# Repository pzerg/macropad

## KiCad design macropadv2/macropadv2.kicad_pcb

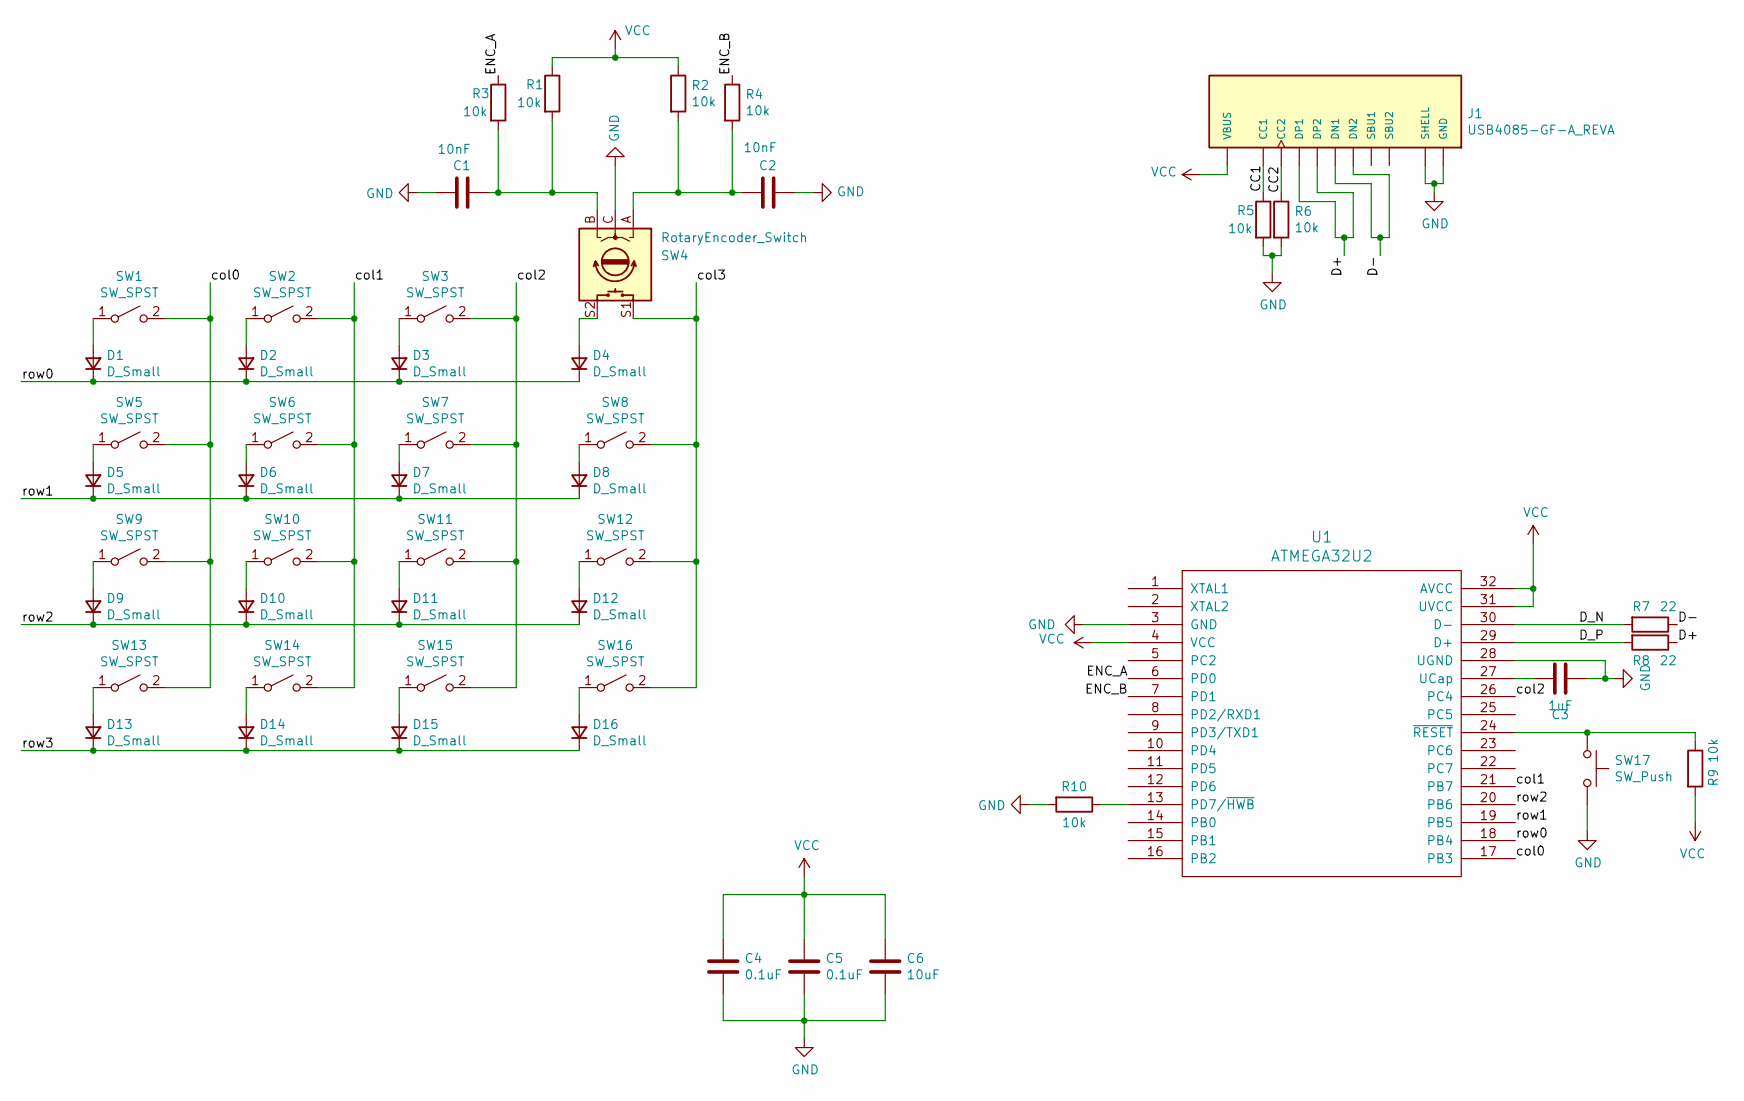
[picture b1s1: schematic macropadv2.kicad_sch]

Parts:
C1, C2: 10nF; C_0603_1608Metric
C3: 1uF; C_0603_1608Metric
C4, C5: 0.1uF; C_0603_1608Metric
C6: 10uF; C_0603_1608Metric
D1, D2, D3, D4, D5, D6, D7, D8, D9, D10, D11, D12, D13, D14, D15, D16: D_Small; D_SOD123W_hand
J1: USB4085-GF-A_REVA; GCT_USB4085-GF-A_REVA; PARTREV A2
R1, R2, R3, R4, R5, R6, R9, R10: 10k; R_0603_1608Metric_Pad0.98x0.95mm_HandSolder
R7, R8: 22; R_0603_1608Metric_Pad0.98x0.95mm_HandSolder
SW1, SW2, SW3, SW5, SW6, SW7, SW8, SW9, SW10, SW11, SW12, SW13, SW14, SW15, SW16: SW_SPST; Kailh_socket_MX
SW4: RotaryEncoder_Switch; PEC11L
SW17: SW_Push; SW_SPST_TL3342
U1: ATMEGA32U2; VQFN-32-1EP_5x5mm_P0.5mm_EP3.15x3.15mm

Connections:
/CC1: J1.A5 (CC1), R5.1
/CC2: J1.B5 (CC2), R6.1
/D+: J1.A6 (DP1), J1.B6 (DP2), R8.1
/D-: J1.A7 (DN1), J1.B7 (DN2), R7.1
/D_N: R7.2, U1.30 (D-)
/D_P: R8.2, U1.29 (D+)
/ENC_A: R3.1, U1.6 (PD0)
/ENC_B: R4.1, U1.7 (PD1)
/col0: SW1.2 (B), SW5.2 (B), SW9.2 (B), SW13.2 (B), U1.17 (PB3)
/col1: SW2.2 (B), SW6.2 (B), SW10.2 (B), SW14.2 (B), U1.21 (PB7)
/col2: SW3.2 (B), SW7.2 (B), SW11.2 (B), SW15.2 (B), U1.26 (PC4)
/col3: SW4.S1, SW8.2 (B), SW12.2 (B), SW16.2 (B)
/row0: D1.1 (K), D2.1 (K), D3.1 (K), D4.1 (K), U1.18 (PB4)
/row1: D5.1 (K), D6.1 (K), D7.1 (K), D8.1 (K), U1.19 (PB5)
/row2: D9.1 (K), D10.1 (K), D11.1 (K), D12.1 (K), U1.20 (PB6)
/row3: D13.1 (K), D14.1 (K), D15.1 (K), D16.1 (K)
GND: C1.2, C2.1, C3.1, C4.1, C5.1, C6.1, J1.A1 (GND), J1.A12 (GND), J1.B1 (GND), J1.B12 (GND), J1.P1 (SHELL), J1.P2 (SHELL), J1.P3 (SHELL), J1.P4 (SHELL), R5.2, R6.2, R10.2, SW4.C, SW17.2, U1.3 (GND), U1.28 (UGND)
unnamed: C1.1, R1.2, R3.2, SW4.B
unnamed: C2.2, R2.2, R4.2, SW4.A
unnamed: C3.2, U1.27 (UCap)
unnamed: D1.2 (A), SW1.1 (A)
unnamed: D2.2 (A), SW2.1 (A)
unnamed: D3.2 (A), SW3.1 (A)
unnamed: D4.2 (A), SW4.S2
unnamed: D5.2 (A), SW5.1 (A)
unnamed: D6.2 (A), SW6.1 (A)
unnamed: D7.2 (A), SW7.1 (A)
unnamed: D8.2 (A), SW8.1 (A)
unnamed: D9.2 (A), SW9.1 (A)
unnamed: D10.2 (A), SW10.1 (A)
unnamed: D11.2 (A), SW11.1 (A)
unnamed: D12.2 (A), SW12.1 (A)
unnamed: D13.2 (A), SW13.1 (A)
unnamed: D14.2 (A), SW14.1 (A)
unnamed: D15.2 (A), SW15.1 (A)
unnamed: D16.2 (A), SW16.1 (A)
unnamed: R9.1, SW17.1, U1.24 (~RESET)
unnamed: R10.1, U1.13 (PD7/~HWB)
VCC: C4.2, C5.2, C6.2, J1.A4 (VBUS), J1.A9 (VBUS), J1.B4 (VBUS), J1.B9 (VBUS), R1.1, R2.1, R9.2, U1.4 (VCC), U1.31 (UVCC), U1.32 (AVCC)

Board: 2 copper layers, 51 parts (30 on the bottom side), 39 nets, no tracks yet.

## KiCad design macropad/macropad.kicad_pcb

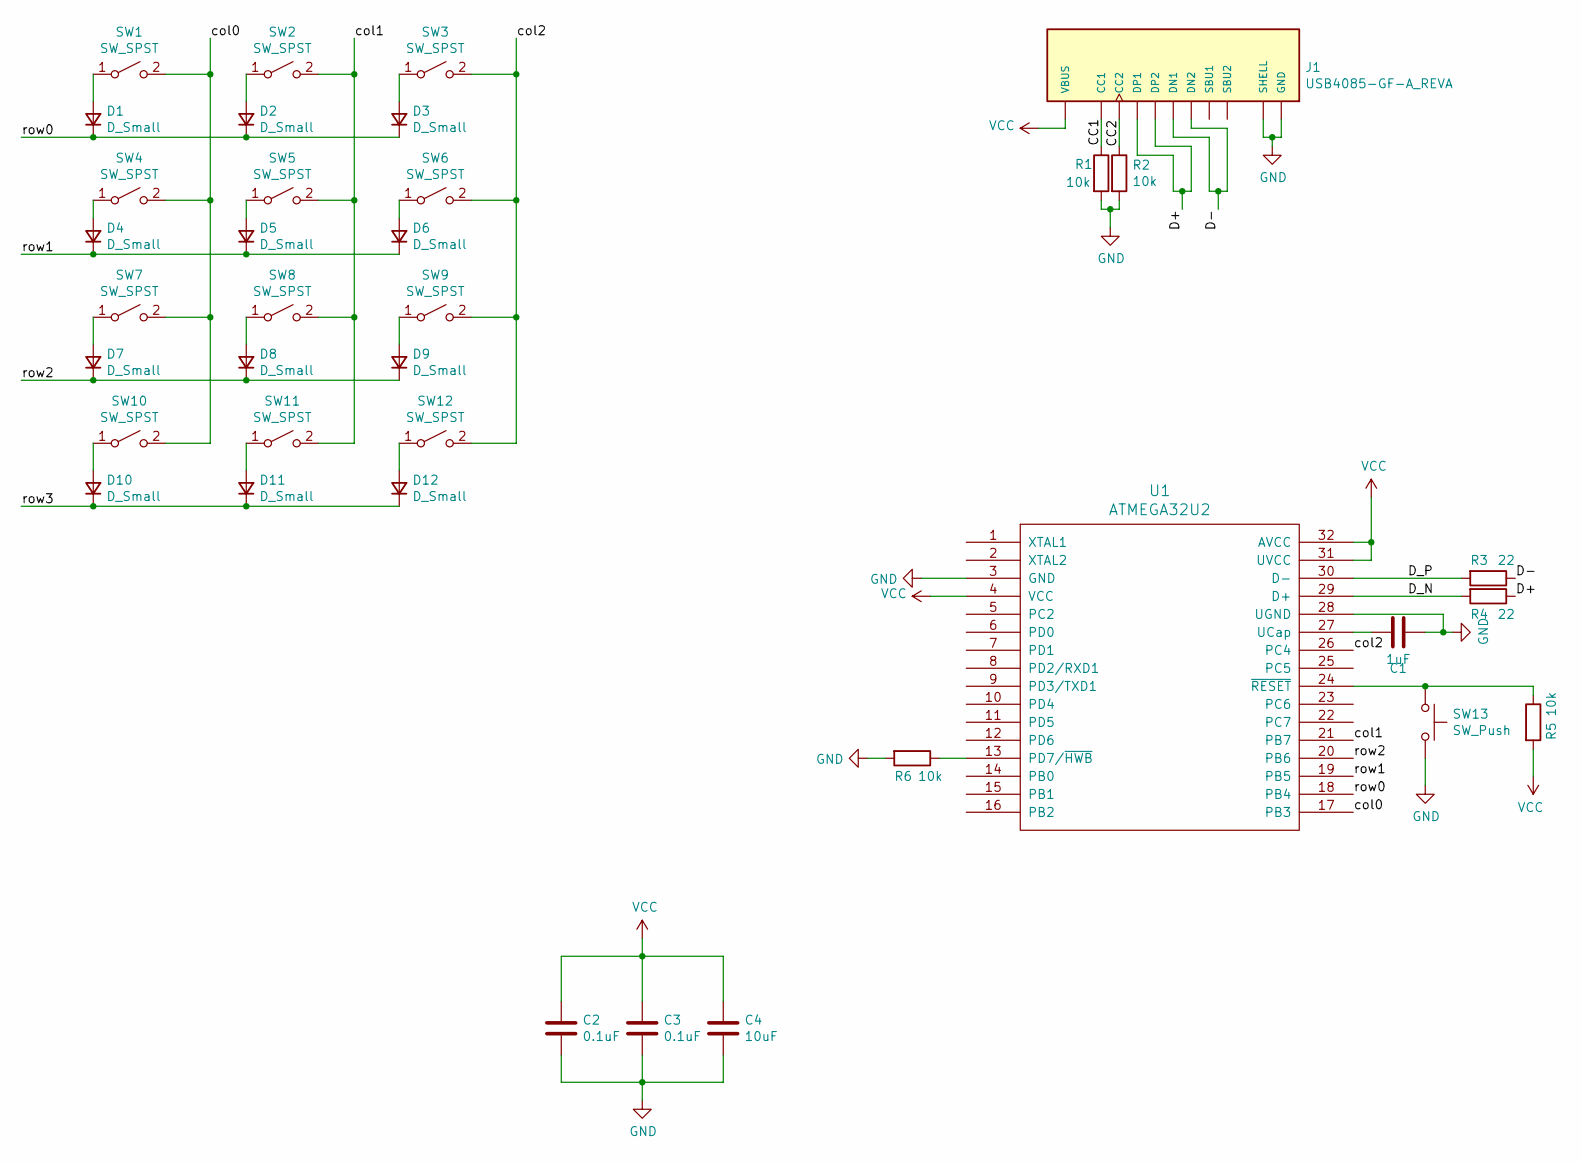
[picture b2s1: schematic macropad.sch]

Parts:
C1: 1uF; C_1608
C2, C3: 0.1uF; C_1608
C4: 10uF; C_1608
D1, D2, D3, D4, D5, D6, D7, D8, D9, D10, D11, D12: D_Small; D_SOD123W_hand
J1: USB4085-GF-A_REVA; GCT_USB4085-GF-A_REVA; PARTREV A2
R1, R2, R5, R6: 10k; R_0603_1608Metric_Pad0.98x0.95mm_HandSolder
R3, R4: 22; R_0603_1608Metric_Pad0.98x0.95mm_HandSolder
SW1, SW2, SW3, SW4, SW5, SW6, SW7, SW8, SW9, SW10, SW11, SW12: SW_SPST; Kailh_socket_MX
SW13: SW_Push; SW_SPST_TL3342
U1: ATMEGA32U2; QFP32

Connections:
/CC1: J1.A5 (CC1), R1.1
/CC2: J1.B5 (CC2), R2.1
/D+: J1.A6 (DP1), J1.B6 (DP2), R4.1
/D-: J1.A7 (DN1), J1.B7 (DN2), R3.1
/D_N: R4.2, U1.29 (D+)
/D_P: R3.2, U1.30 (D-)
/col0: SW1.2 (B), SW4.2 (B), SW7.2 (B), SW10.2 (B), U1.17 (PB3)
/col1: SW2.2 (B), SW5.2 (B), SW8.2 (B), SW11.2 (B), U1.21 (PB7)
/col2: SW3.2 (B), SW6.2 (B), SW9.2 (B), SW12.2 (B), U1.26 (PC4)
/row0: D1.1 (K), D2.1 (K), D3.1 (K), U1.18 (PB4)
/row1: D4.1 (K), D5.1 (K), D6.1 (K), U1.19 (PB5)
/row2: D7.1 (K), D8.1 (K), D9.1 (K), U1.20 (PB6)
/row3: D10.1 (K), D11.1 (K), D12.1 (K)
GND: C1.1, C2.1, C3.1, C4.1, J1.A1 (GND), J1.A12 (GND), J1.B1 (GND), J1.B12 (GND), J1.P1 (SHELL), J1.P2 (SHELL), J1.P3 (SHELL), J1.P4 (SHELL), R1.2, R2.2, R6.2, SW13.2, U1.3 (GND), U1.28 (UGND)
unnamed: C1.2, U1.27 (UCap)
unnamed: D1.2 (A), SW1.1 (A)
unnamed: D2.2 (A), SW2.1 (A)
unnamed: D3.2 (A), SW3.1 (A)
unnamed: D4.2 (A), SW4.1 (A)
unnamed: D5.2 (A), SW5.1 (A)
unnamed: D6.2 (A), SW6.1 (A)
unnamed: D7.2 (A), SW7.1 (A)
unnamed: D8.2 (A), SW8.1 (A)
unnamed: D9.2 (A), SW9.1 (A)
unnamed: D10.2 (A), SW10.1 (A)
unnamed: D11.2 (A), SW11.1 (A)
unnamed: D12.2 (A), SW12.1 (A)
unnamed: R5.1, SW13.1, U1.24 (~RESET)
unnamed: R6.1, U1.13 (PD7/~HWB)
VCC: C2.2, C3.2, C4.2, J1.A4 (VBUS), J1.A9 (VBUS), J1.B4 (VBUS), J1.B9 (VBUS), R5.2, U1.4 (VCC), U1.31 (UVCC), U1.32 (AVCC)

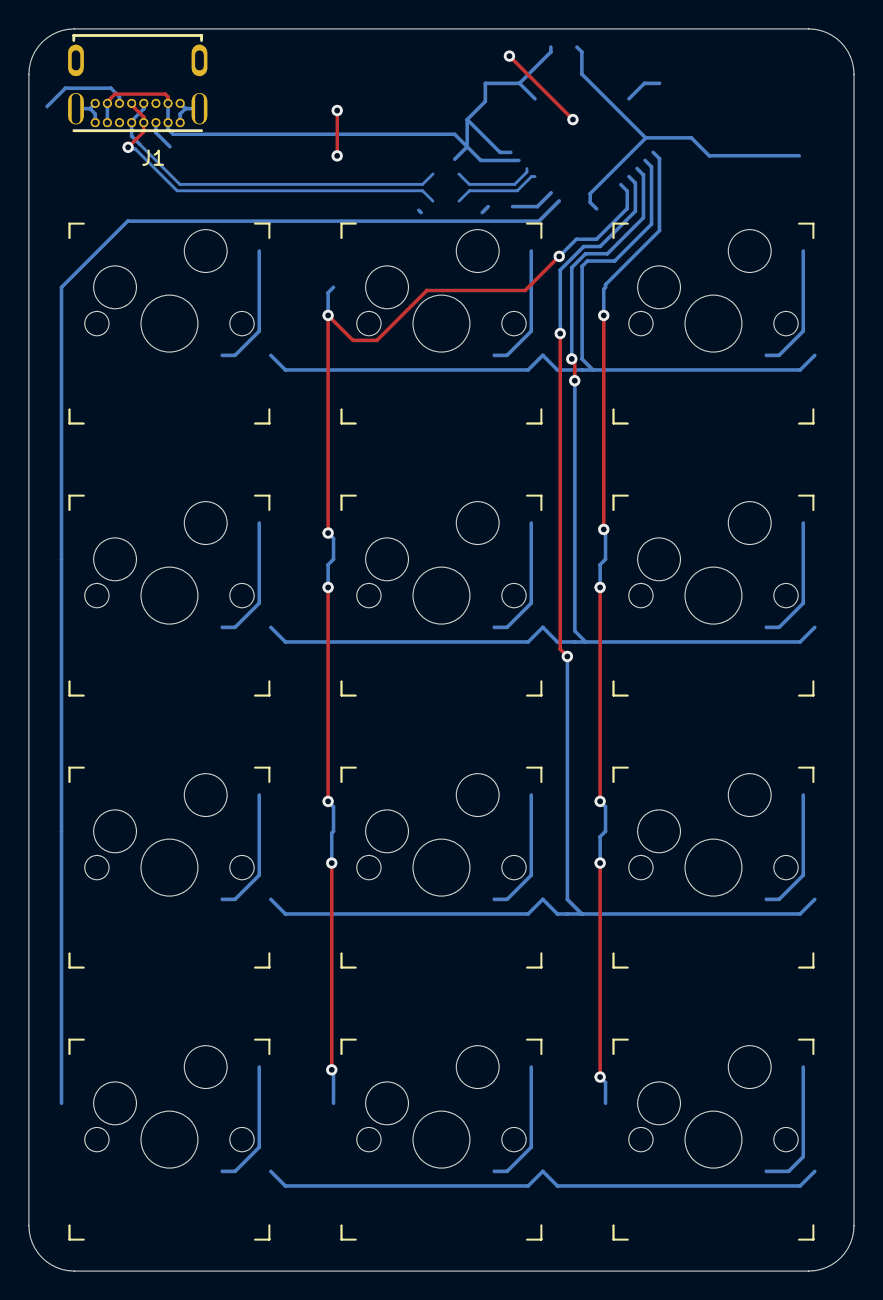
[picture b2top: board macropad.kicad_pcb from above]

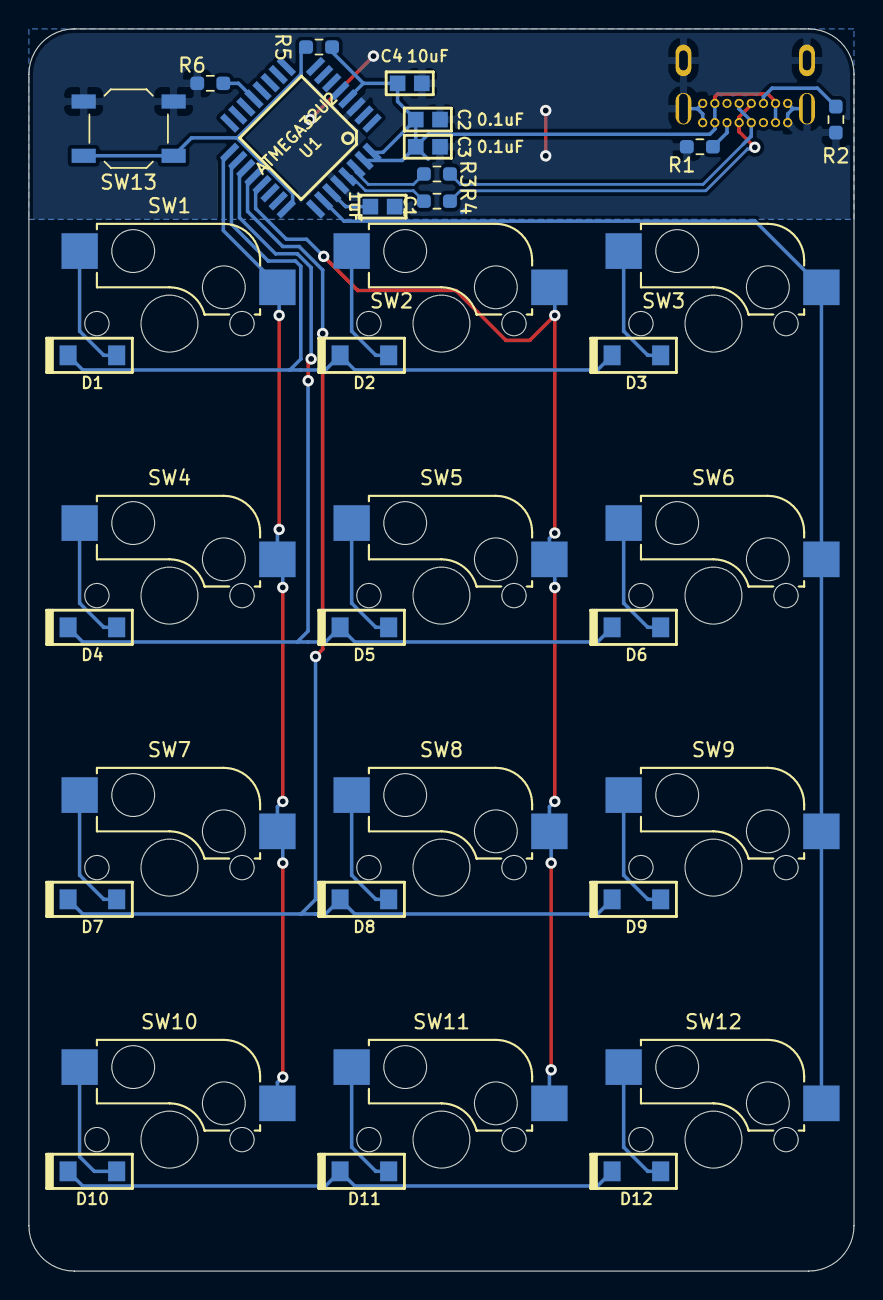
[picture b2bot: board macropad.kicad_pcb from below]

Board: 2 copper layers, 57.8 x 87.0 mm, 37 parts (24 on the bottom side), 30 nets.

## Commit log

2021-10-08 started
2022-06-23 added encoder
